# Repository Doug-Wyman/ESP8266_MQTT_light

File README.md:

# ESP8266_MQTT_light
Micropython code for controlling an RGB and White light 
using an ESP8266 controller board of my design

This code is poorly written alpha code to control a 12 VDC RGB light 
and a 12 VDC white light using MQTT. It works but needs improvement. 

The switches control on/off with a short press and dimming/brightening 
when they are held down.  

OSH Park is making my controller board (click on image)
<a href="https://oshpark.com/shared_projects/GQtievsf">
</img></a>.  
The design is an Eagle cad design but there is a caveat!!
The switches come with 4 pins two pair of bussed through hole.
However even though the foot print is identical there are 
two varieties.  With the opposite connections. The board traces
will show the bussed pairs.

Being very new to ESP8266 and micropython it seems as though the code 
is near the memory limit of the ESP8266.
So I have eliminated all comments and extras.  
I welcome suggestions and corrections.  

The entire project is for a Home-Assistant installation.
I have 4 sets of lights working. I was experiencing disconnect fails 
when either the HASS server or the Mosquitto server was rebooted 
so I wrote the code so it reboots the ESP8266
GPIO-16 controlls the blue LED on the ESP8266 board I am using so the
code turns it on during boot then off once booted.  So it acts as an
indicator of when the board is in boot mode.

I have included a sample configuration for Home Assistant control of the module.
The script will return the version which will fill the sensor value.

The Code:
boot.py starts by loading the webrepl which probably won't be needed in production.
The parameters file is loaded and contains data for the WiFi connection, 
the MQTT instance, the pin data for the ESP8266 and such.

The status file is essentially the JSON state last saved so the light on boot 
is set to the last known state. 

Boot then calls main.  Main starts by opening the MQTT connection.
If there is an error in connecting, the program flashes the LED on the ESP8266 three times 
in a one second on one second off and exits.

On a good MQTT connection , the routine sets a callback address for received messages 
and returns the connected client.

The code enters the main loop. It does an MQTT message check first then 
the state of the switches is checked.  A short press/release will toggle the on/off state.
After the button is held down for a period longer than the counter is set for,
the light goes into a brighten/dim cycle.

After any change in state, the state file is updated and an MQTT status message is sent.
The last thing in the loop is a check to see when we sent the last status and
to send an update when timed out.

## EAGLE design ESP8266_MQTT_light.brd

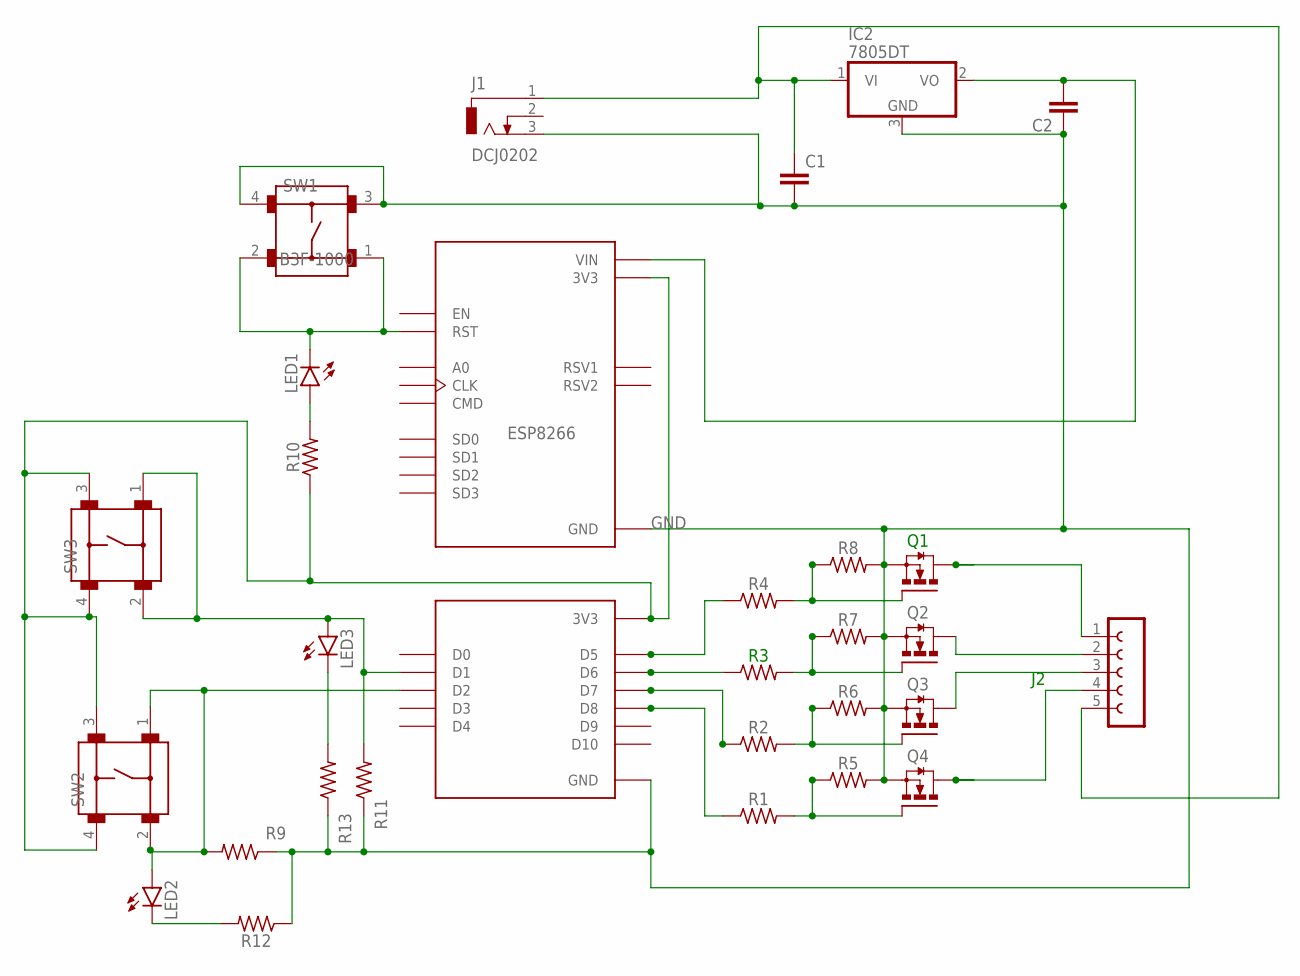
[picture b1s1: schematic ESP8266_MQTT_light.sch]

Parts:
C1, C2: CC1005; C1005
ESP8266: 113990105; SEEED_113990105
IC2: 7805DT; TO252
J1: DCJ0202
J2: RGBW1; FE05W
LED1, LED2, LED3: LEDCHIPLED_1206; CHIPLED_1206
Q1, Q2, Q3, Q4: IRF3704S; D2PACK
R1, R2, R3, R4: 1k; R1206
R5, R6, R7, R8, R9, R11: 10k; R1206
R10, R12, R13: 33; R1206
SW1, SW2, SW3: B3F-1000

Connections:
3.3VDC: ESP8266.J1_11 (3V3), ESP8266.J2_6 (3V3), ESP8266.J2_15 (3V3), R10.1, SW2.3, SW2.4, SW3.3, SW3.4
5VDC: C2.2, ESP8266.J1_15 (VIN), IC2.2 (VO)
12VDC: C1.1, IC2.1 (VI), J1.1, J2.5
B-IN: Q2.1 (G), R3.2, R7.1
B-MAIN: ESP8266.J2_9 (D6), R3.1
B-OUT: J2.2, Q2.2 (D)
G-IN: Q3.1 (G), R2.2, R6.1
G-MAIN: ESP8266.J2_10 (D7), R2.1
G-OUT: J2.3, Q3.2 (D)
GND: C1.2, C2.1, ESP8266.J1_10 (GND), ESP8266.J1_14 (GND), ESP8266.J2_7 (GND), ESP8266.J2_14 (GND), IC2.3 (GND), J1.3, Q1.3 (S), Q2.3 (S), Q3.3 (S), Q4.3 (S), R5.2, R6.2, R7.2, R8.2, R9.1, R11.1, R12.1, R13.1, SW1.3, SW1.4
unnamed: LED1.A, R10.2
unnamed: LED2.C, R12.2
unnamed: LED3.C, R13.2
unnamed: ESP8266.J2_3 (D2), LED2.A, R9.2, SW2.1, SW2.2
R-IN: Q4.1 (G), R1.2, R5.1
R-MAIN: ESP8266.J2_11 (D8), R1.1
R-OUT: J2.4, Q4.2 (D)
RESET: ESP8266.J1_13 (RST), LED1.C, SW1.1, SW1.2
W-CTL: ESP8266.J2_2 (D1), LED3.A, R11.2, SW3.1, SW3.2
W-IN: Q1.1 (G), R4.2, R8.1
W-MAIN: ESP8266.J2_8 (D5), R4.1
W-OUT: J2.1, Q1.2 (D)

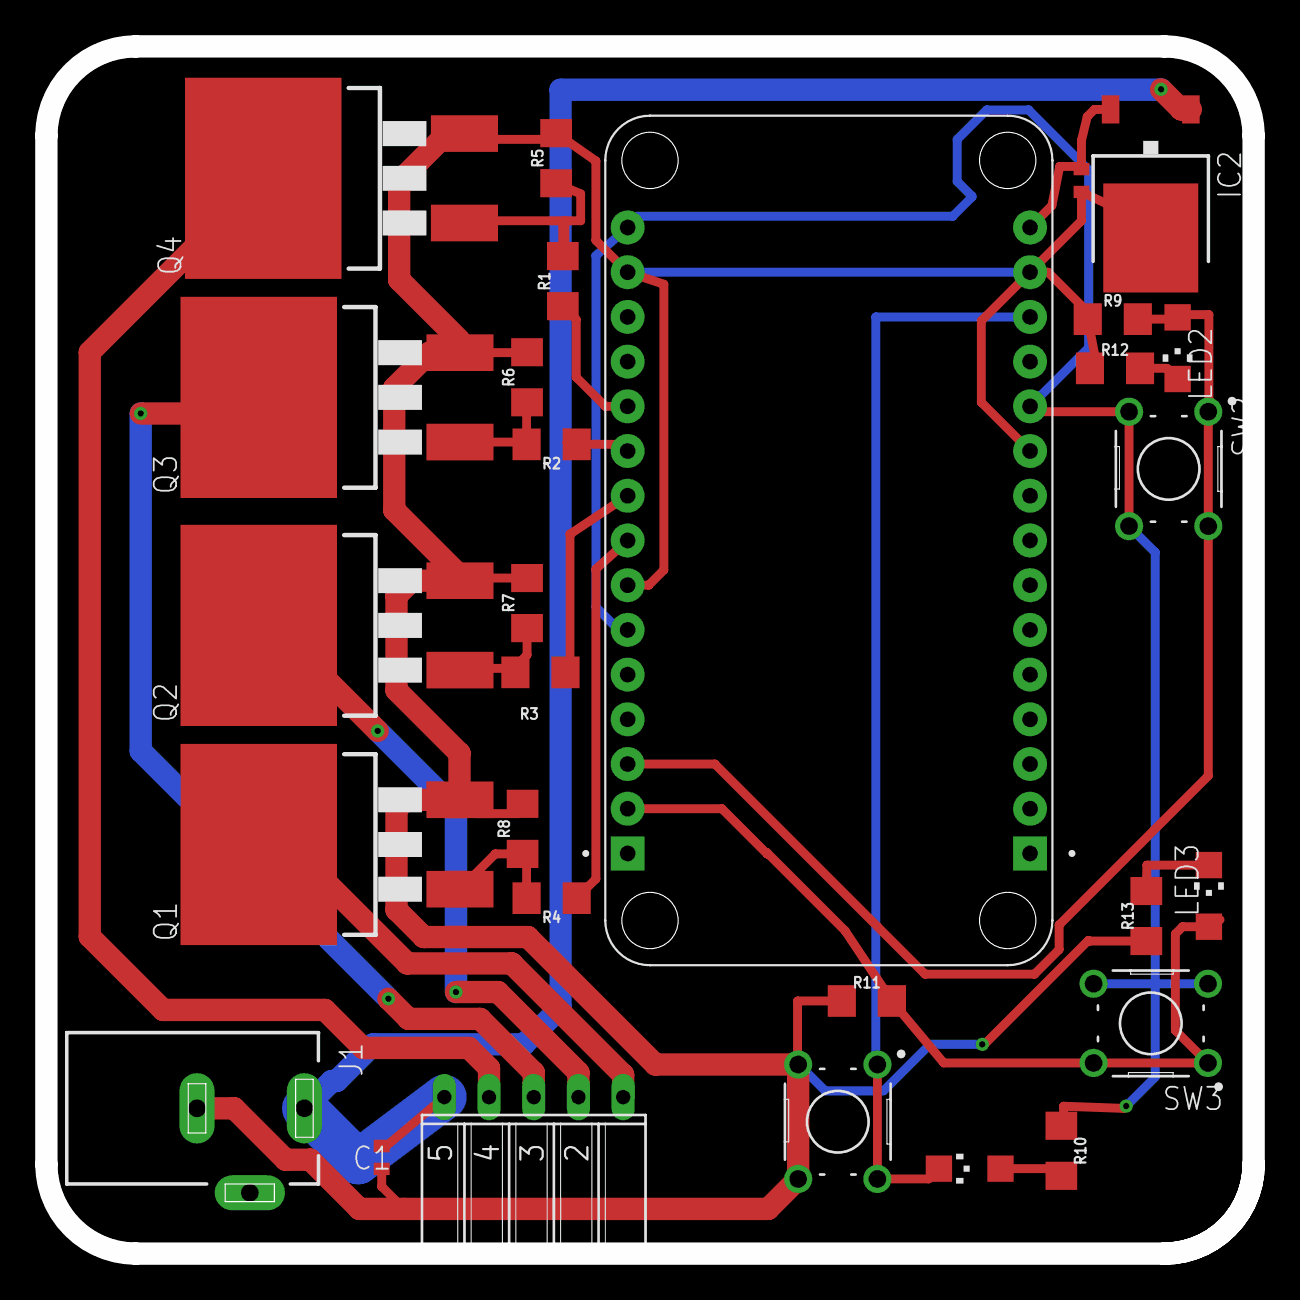
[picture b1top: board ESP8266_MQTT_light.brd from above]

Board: 2 copper layers, 68.6 x 68.6 mm, 29 parts (0 on the bottom side), 22 nets.

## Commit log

2021-04-12 paring off unneeded code to keep within available memory.
2021-04-12 added mentions of Home Assistant
2021-04-17 ESP8266 MQTT light
2021-04-20 Changed Switch on board
    The original board had an error on the switch
2021-04-21 A revised board and caveat
2021-05-18 Changed Resistor footprint
    I changed the resistors to a 1206 SMD footprint
2021-05-19 Board corrections
    Corrected amended board to allo for the larger 1206 resistors
2021-09-24 Update main.py
    Changed so that the version is sent on client connect as an aid to Home Assistant use
2022-08-24 Update main.py
    Changed from a separate MQTT code to the new built inMicropython umqtt.
2022-08-24 Delete umqttsimple.py
    No longer needed as Micropython now has umqtt built in
